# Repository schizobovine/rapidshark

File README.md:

# RapidShark
Nerf RapidStrike CS-18 mod using an Arduino and LiPo battery upgrade to rain
foamy annoyance upon one's enemies.

The name originally came from my initial idea to use a pair of NSR Shark 40krpm
motors, originally for 12V slot car racing. It quickly became a reference to
Randall Munroe's [XKCD comic about lowering one's standards for success as a
project wears on...]<https://xkcd.com/349/>

# Versions

This project has undergone a number of major and minor redesigns, and my
documentation isn't exactly the best, especially for earlier versions where I
assumed this would be a quick hack involving relatively little electronics
knowledge (oh, to be 3 years younger and less naive...).

* Mark I
*  Completed build
*  Used slightly larger motors: 24mm 12V 12850rpm [PAN14EE12AA1]<http://www.digikey.com/product-detail/en/PAN14EE12AA1/P14346-ND/2417070>
*  Covered cut-outs for above with some horribly done epoxy work
*  4S LiPo battery (14.8V nominal)
*  Flywheels ran directly off battery voltage
*  Rate of fire controlled via diodes (1N5209's?) in series
*  Segmented LED display only showed battery voltage.
*  Extremely noisy, had jamming issues especially at higher ROF
*  Very clumsy controls (giant knob on the side for ROF)
*  Overall, kinda crappy prototype

* Mark II
*  Never finished build
*  Originally going to be 2S LiPo based
*  Proved too noisy for reasonable use

* Mark III
*  Completed build
*  Same [PAN14EE12AA1]<http://www.digikey.com/product-detail/en/PAN14EE12AA1/P14346-ND/2417070> as in Mark I
*  Used heat gun to deform plastic to accomodate motors
*  4S LiPo battery (14.8V nominal)
*  Flywheels again directly off line voltage
*  Rate of fire controlled via stupidly big linear regulator (LM335, then LT1083)
*  Custom PCB from OSHPark for speed controller
*  Actually bothered to paint this one
*  Slightly better slide switch for ROF control
*  Added pushbutton laser "sight" because reasons
*  First attempt at ammo counter using SparkFun Pro Mini 5V to drive a 2 digit segmented display
*  Detected shots at first using IR LED & photodiode, but was too noisy so went to reed switch
*  Button panel for fiddling with/resetting counter
*  Counter was awesome but proved very unreliable in practice
*  Noticable voltage drop-out during flywheel spin-up

* Mark IV
*  Work in progess
*  Skipping paint job to make this one a "sleeper" model
*  Motors unselected but will be 130 Mabuchi form-factor to fit in existing case with little modification
*  Will feature two proper H-bridges, the [Pololu VNH5019 Motor Driver Carrier]<https://www.pololu.com/product/1451>
*  Since the H-bridges will be electronically controlled, switched to subminiature microswitches hooked up to uC (instead of giant 15A microswitches directly flipping current around)
*  [Adafruit Metro Mini]<https://www.adafruit.com/products/2590> as main controller
*  OLED display (either SparkFun Microview or Ye Olde Generic From Ebay)
*  IR interrupter for dart firing detection confirmation, in combination with mechanical position detection for the dart pusher.
*  Whole slew of small custom PCB's to aid in wiring

# License

* AVR C code (basically, everything under the firmware directory) is licensed under the GPLv2.0.
* Everything else is Creative Commons 4.0, Attribution-Share-Sharealike (CC-4.0-BY-SA)

# Acknowledgements

I would not be nearly as far along (or in the ICU from exploding batteries) if
not for the help and previous work & knowledge of
[torukmakto4]<http://torukmakto4.blogspot.co.uk/>; read some of the linked
posts below for a good breakdown of the basic fire control circuit in the
RapidStrike.

I also would like to thank the folks from Blastersmiths UK for their
information shared on [Diaries of a Nerf
Armorurer]<http://nerfarmourer.tumblr.com>, as it both provided inspiration,
guidance, and a lot of helpful pictures for this project.

# References

[The Dart Zone: Wiring and electrical practices]<http://torukmakto4.blogspot.co.uk/2013/04/tech-wiring-and-electrical-practices.html>
[The Dart Zone: Standard Rapidstrike, an Illustrated Guide]<http://torukmakto4.blogspot.co.uk/2013/10/standard-rapidstrike-illustrated-guide.html>
[The Dart Zone: Why compensating for resistance using additional voltage is bad design]<http://torukmakto4.blogspot.co.uk/2014/05/why-compensating-for-resistance-using.html>
[Diaries of a Nerf Armourer: 'Sharked' Rapidstrike CS-18 - Raja and Triakis]<http://nerfarmourer.tumblr.com/post/59029888581/sharked-rapidstrike-cs-18-raja-and-triakis>
[Diaries of a Nerf Armourer: NSR Shark 40 Necrospy]<http://nerfarmourer.tumblr.com/post/69776618533/nsr-shark-40-necrospy>
[Diaries of a Nerf Armourer: Rapidstrike Modification Guide]<http://nerfarmourer.tumblr.com/post/57957334515/rapidstrike-modification-guide-also-commissions>

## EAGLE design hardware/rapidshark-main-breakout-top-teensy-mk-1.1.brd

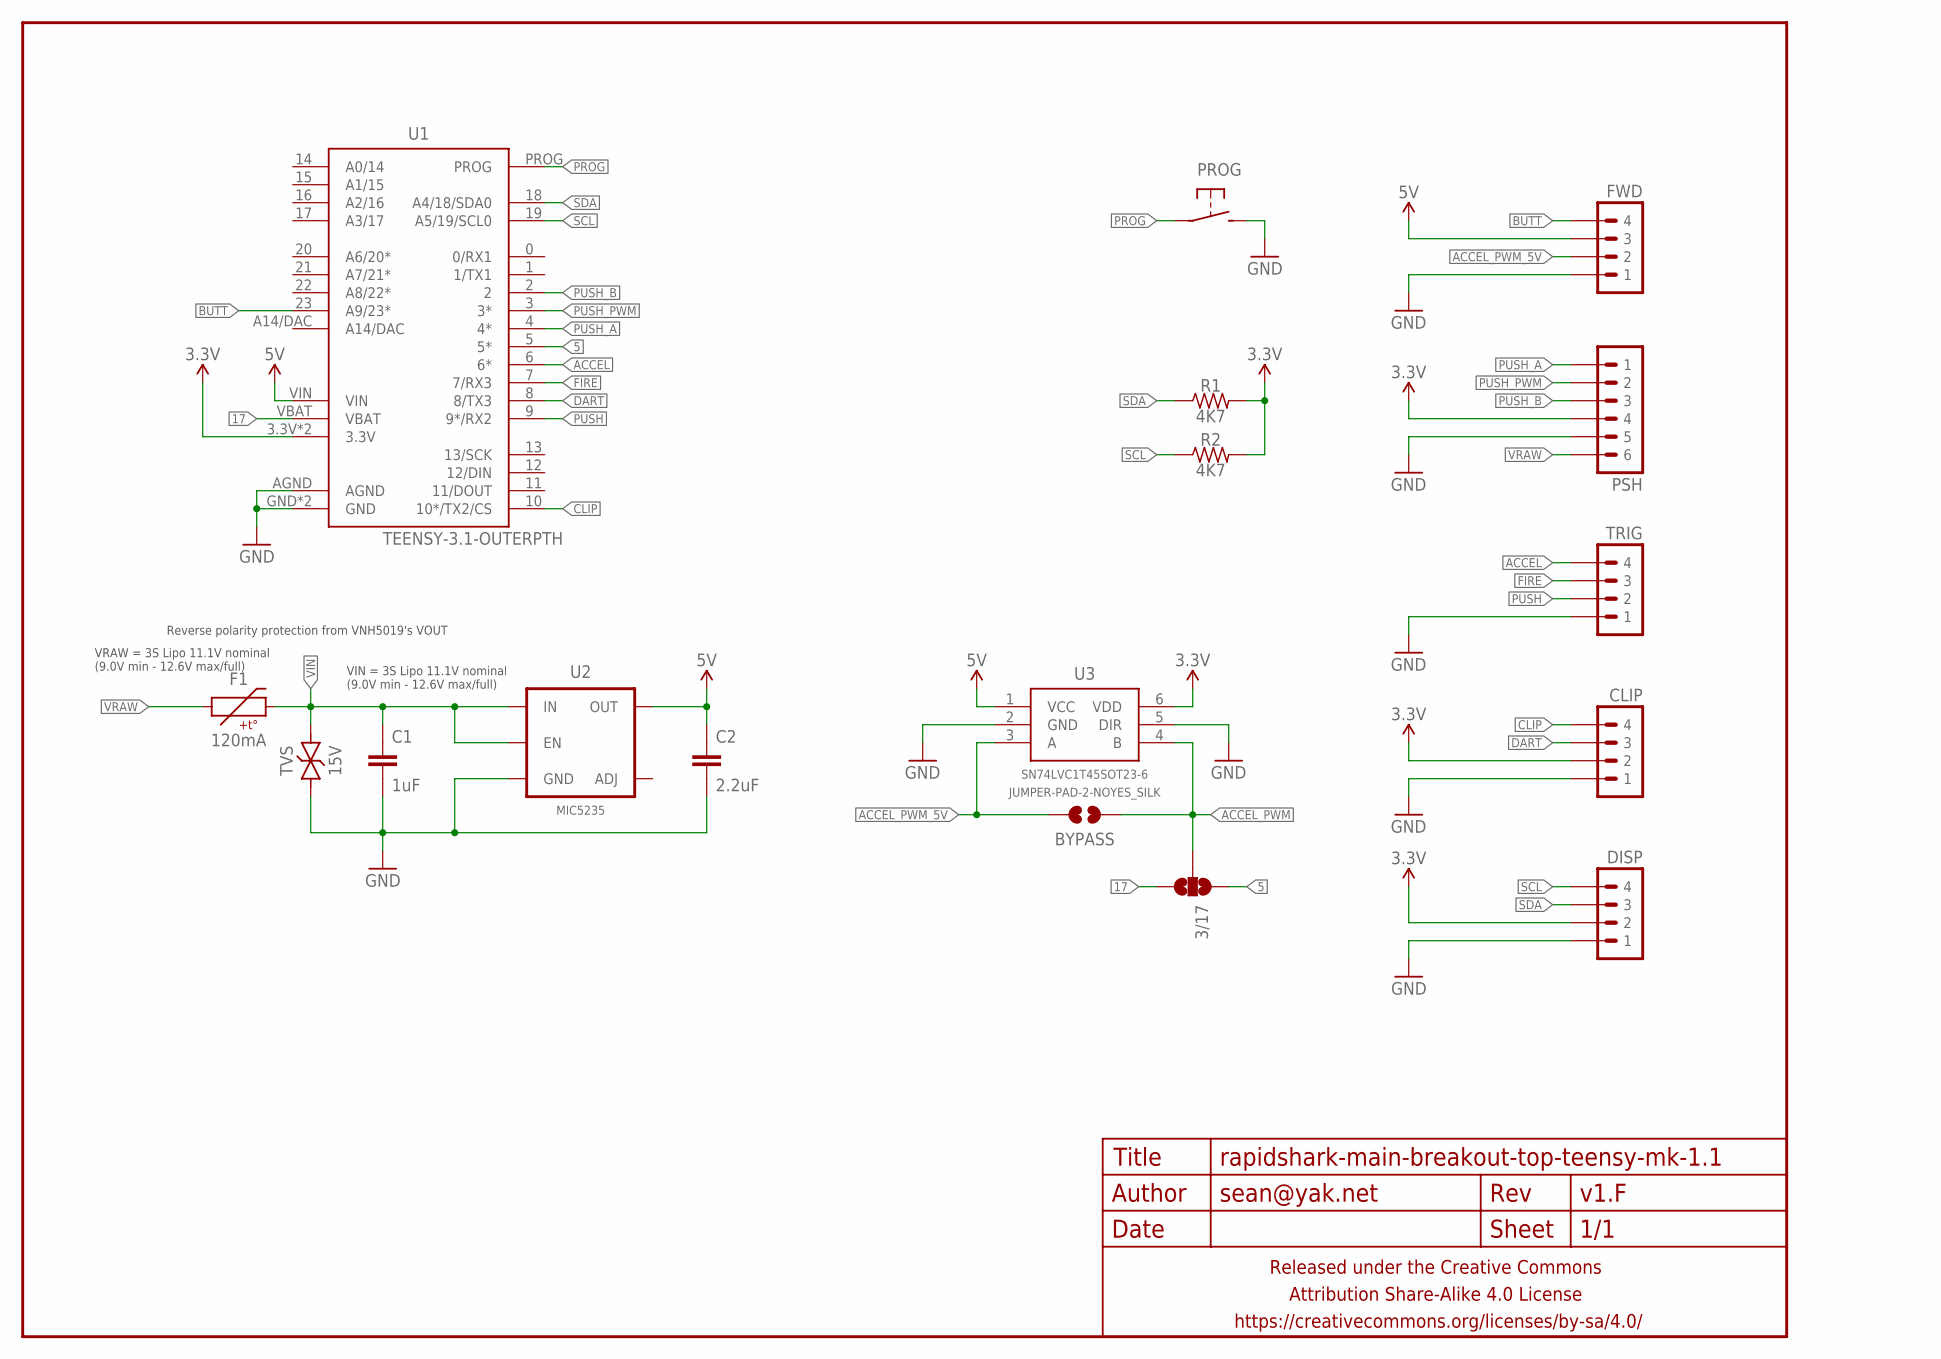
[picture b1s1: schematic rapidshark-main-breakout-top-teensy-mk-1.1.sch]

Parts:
3/17: JUMPER-PAD-3-NOSMALLER; PAD-JUMPER-3-NO_YES_SILK_FULL_BOX_SMALLER
BYPASS: JUMPER-PAD-2-NOYES_SILK; PAD-JUMPER-2-NO_YES_SILK
C1: 1uF; C0603-TIGHTER
C2: 2.2uF; C0603-TIGHTER
CLIP: M04JST-PTH-VERT; JST-4-PH-VERT-PTH
DISP: M04JST-PTH-VERT; JST-4-PH-VERT-PTH
F1: 120mA; PTC-1206
FRAME1: FRAME-LETTERNO_PACKAGE; DUMMY
FWD: M04JST-PTH-VERT; JST-4-PH-VERT-PTH
PROG: SPST-NO-TACTCK-PTS840-GK; TACTILE-SMD-CK-PTS840-GK
PSH: M06JST-PH-PTH-VERT; JST-6-PH-VERT-PTH
R1, R2: 4K7; R0603-TIGHTER
TRIG: M04JST-PTH-VERT; JST-4-PH-VERT-PTH
TVS: 15V; SMA-DIODE-TVS-BIDIR
U1: TEENSY-3.1-OUTERPTH; TEENSY-3.1_OUTERONLY
U2: MIC5235; SOT23-5
U3: SN74LVC1T45SOT23-6; SOT23-6

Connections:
3.3V: CLIP.2, DISP.2, PSH.4, R1.2, R2.2, U1.3.3V, U1.3V (3.3V), U3.6 (VDD)
5: 3/17.1, U1.5 (5*)
5V: C2.1, FWD.3, U1.VIN, U2.5 (OUT), U3.1 (VCC)
17: 3/17.3, U1.VBAT
ACCEL: TRIG.4, U1.6 (6*)
ACCEL_PWM: 3/17.2, BYPASS.1, U3.4 (B)
ACCEL_PWM_5V: BYPASS.2, FWD.2, U3.3 (A)
BUTT: FWD.4, U1.23 (A9/23*)
CLIP: CLIP.4, U1.10 (10*/TX2/CS)
DART: CLIP.3, U1.8 (8/TX3)
FIRE: TRIG.3, U1.7 (7/RX3)
GND: C1.2, C2.2, CLIP.1, DISP.1, FWD.1, PROG.3 (2), PROG.4 (2), PSH.5, TRIG.1, TVS.1, U1.AGND, U1.GND, U1.GND1 (GND), U2.2 (GND), U3.2 (GND), U3.5 (DIR)
PROG: PROG.1, PROG.2 (1), U1.PROG
PUSH: TRIG.2, U1.9 (9*/RX2)
PUSH_A: PSH.1, U1.4 (4*)
PUSH_B: PSH.3, U1.2
PUSH_PWM: PSH.2, U1.3 (3*)
SCL: DISP.4, R2.1, U1.19 (A5/19/SCL0)
SDA: DISP.3, R1.1, U1.18 (A4/18/SDA0)
VIN: C1.1, F1.2, TVS.2, U2.1 (IN), U2.3 (EN)
VRAW: F1.1, PSH.6

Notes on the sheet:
VIN = 3S Lipo 11.1V nominal (9.0V min - 12.6V max/full)
VRAW = 3S Lipo 11.1V nominal (9.0V min - 12.6V max/full)
Reverse polarity protection from VNH5019's VOUT

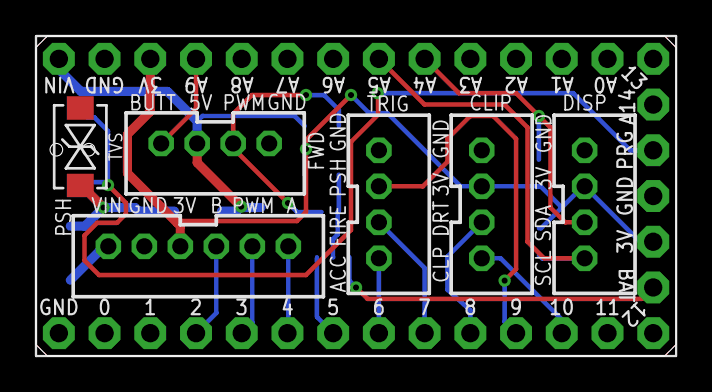
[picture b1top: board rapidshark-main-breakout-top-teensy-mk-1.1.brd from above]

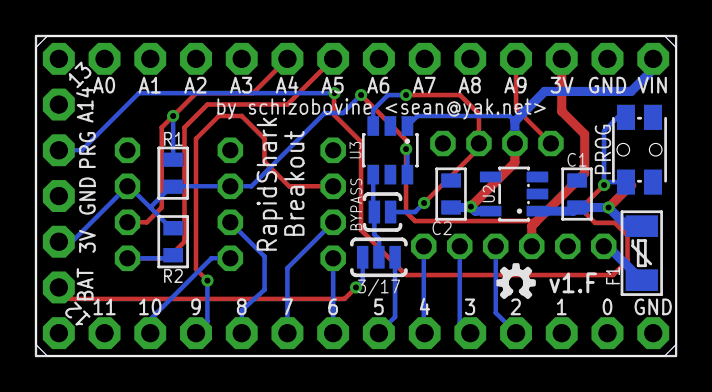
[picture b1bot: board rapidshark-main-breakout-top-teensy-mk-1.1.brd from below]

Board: 2 copper layers, 35.6 x 17.8 mm, 19 parts (12 on the bottom side), 21 nets.

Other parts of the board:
U$3: OSHWLOGO_TINY_SILKONLY

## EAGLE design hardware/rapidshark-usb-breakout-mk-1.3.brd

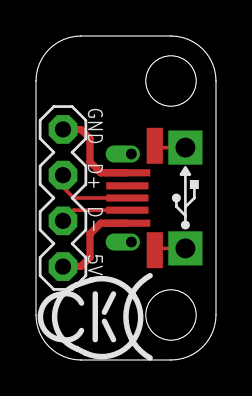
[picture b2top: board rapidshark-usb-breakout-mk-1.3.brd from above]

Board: 2 copper layers, 10.0 x 18.0 mm, 4 parts (1 on the bottom side), 4 nets.

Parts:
FRAME1: FRAME-LETTERNO_PACKAGE; DUMMY
JP1: M04PTH-CENTERED; 1X04-PTH-VERT-CENTER
U$1: COW_SMALL_NOTEXT
USB1: USB-AB-SHIELDFCI-10103594-USB-MICRO-B-EVENLESS; FCI-10103594-USB-MICRO-B-EVENLESS

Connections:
5V: JP1.4, USB1.1
DATA_M: JP1.3, USB1.2
DATA_P: JP1.2, USB1.3
GND: JP1.1, USB1.5, USB1.SHIELD@1, USB1.SHIELD@2, USB1.SHIELD@3, USB1.SHIELD@4, USB1.SHIELD@5, USB1.SHIELD@6

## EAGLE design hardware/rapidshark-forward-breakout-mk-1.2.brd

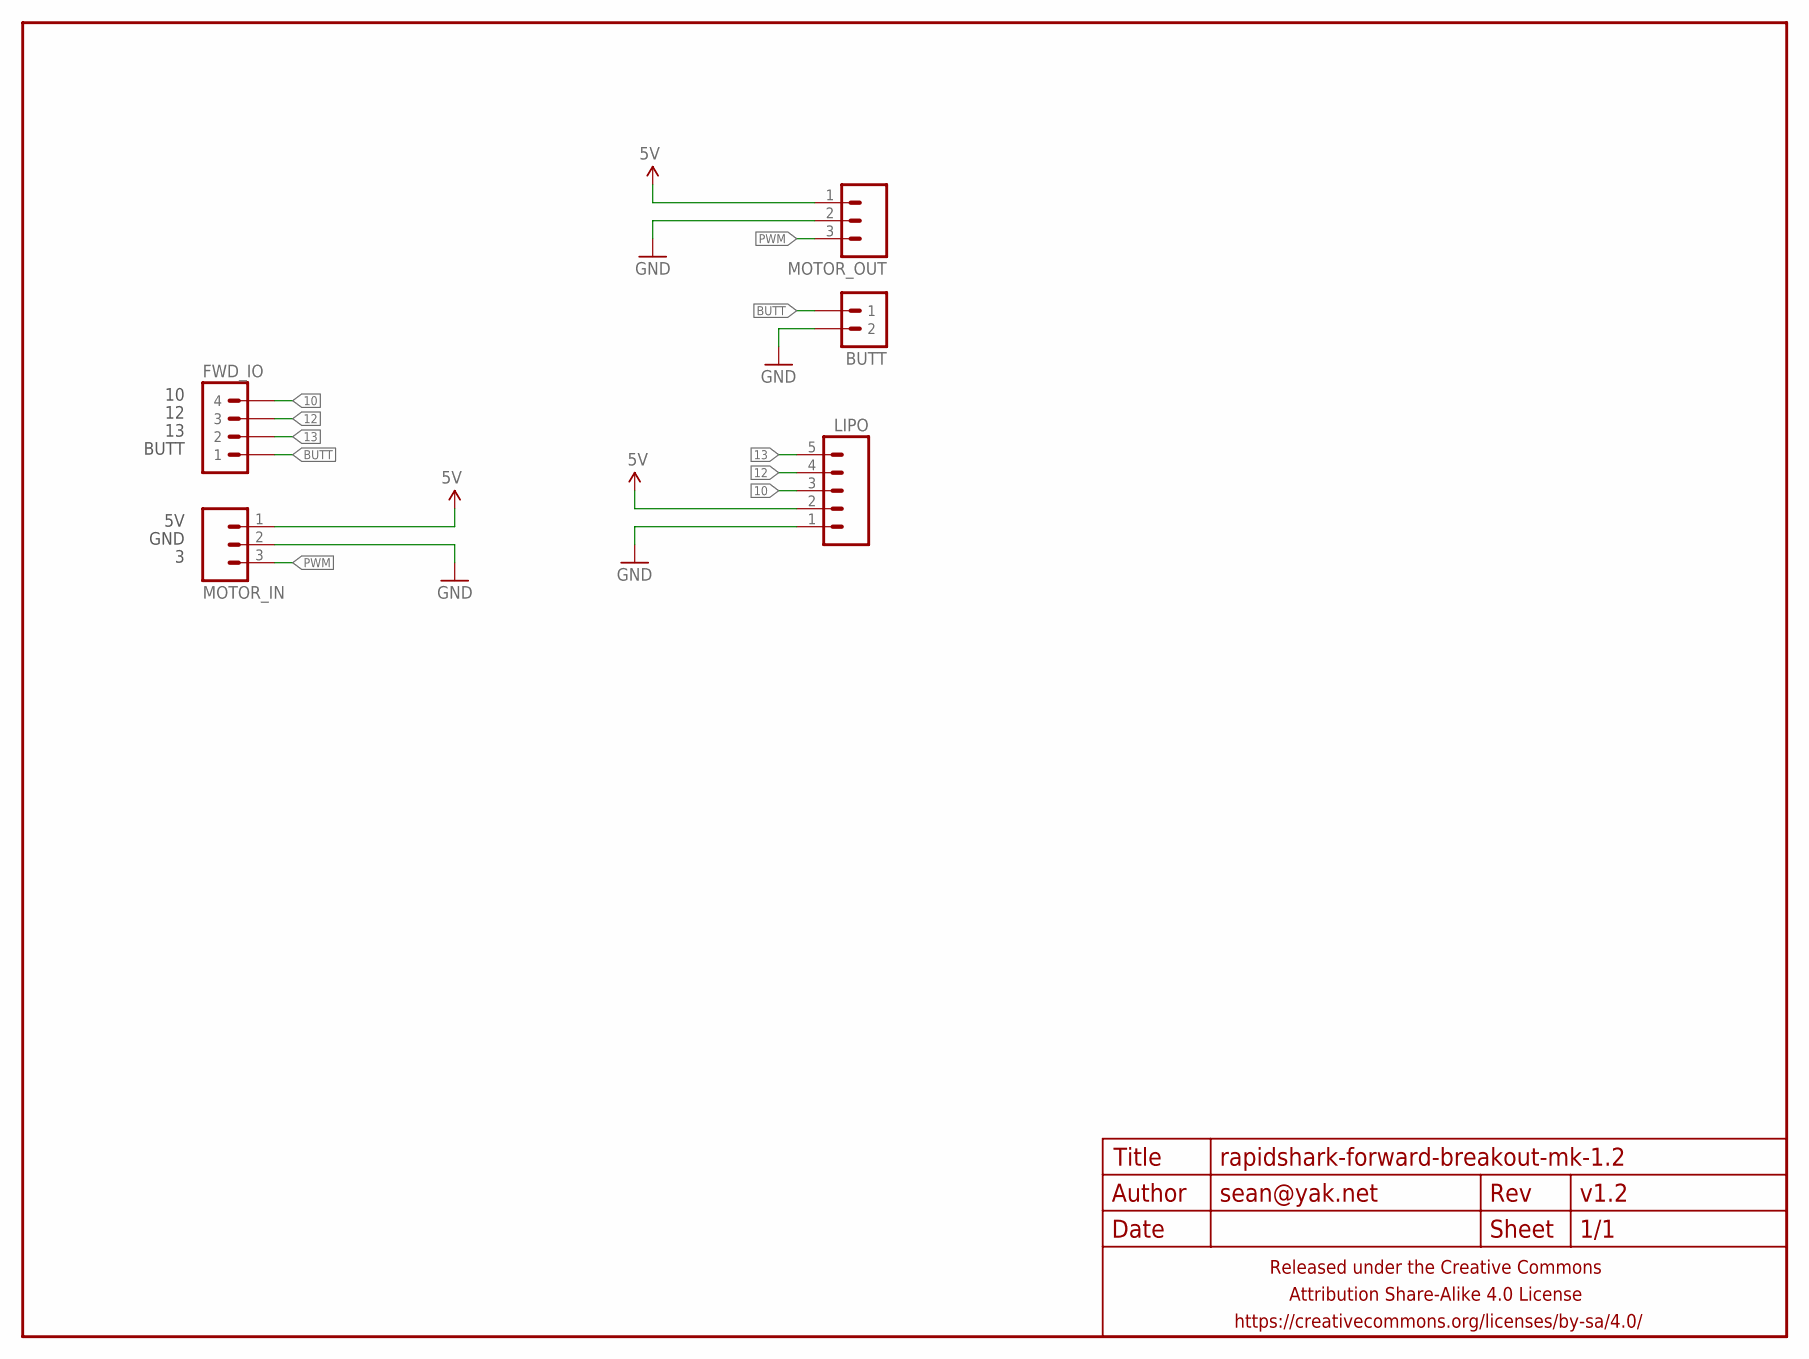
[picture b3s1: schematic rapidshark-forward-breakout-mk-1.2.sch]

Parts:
BUTT: M02JST-PTH-VERT; JST-2-PH-VERT-PTH
FRAME1: FRAME-LETTERNO_PACKAGE; DUMMY
FWD_IO: M04JST-PTH-VERT; JST-4-PH-VERT-PTH
LIPO: M05JST-PH-VERT-PTH; JST-5-PH-VERT-PTH
MOTOR_IN: M03JST-PTH-VERT; JST-3-PH-VERT-PTH
MOTOR_OUT: M03JST-PTH-VERT; JST-3-PH-VERT-PTH

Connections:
5V: LIPO.2, MOTOR_IN.1, MOTOR_OUT.1
10: FWD_IO.4, LIPO.3
12: FWD_IO.3, LIPO.4
13: FWD_IO.2, LIPO.5
BUTT: BUTT.1, FWD_IO.1
GND: BUTT.2, LIPO.1, MOTOR_IN.2, MOTOR_OUT.2
PWM: MOTOR_IN.3, MOTOR_OUT.3

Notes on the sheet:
GND
BUTT

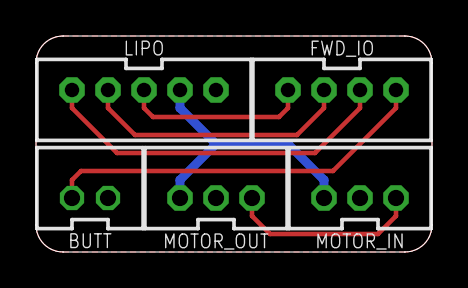
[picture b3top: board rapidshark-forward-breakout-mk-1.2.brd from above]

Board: 2 copper layers, 22.0 x 12.0 mm, 6 parts (1 on the bottom side), 7 nets.

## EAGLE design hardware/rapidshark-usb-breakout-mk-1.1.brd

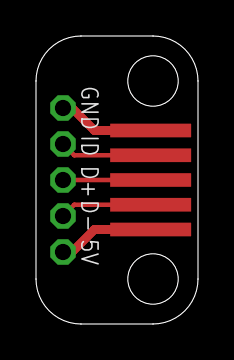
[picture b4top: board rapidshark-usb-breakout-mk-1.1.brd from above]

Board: 2 copper layers, 9.0 x 16.0 mm, 3 parts (1 on the bottom side), 5 nets.

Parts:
FRAME1: FRAME-LETTERNO_PACKAGE; DUMMY
JP1: M052MMPTH; 1X05-0.9X2MM-PTH
U1: ADAFRUIT_USB_PANEL_MOUNT

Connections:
5V: JP1.5, U1.5
DATA_M: JP1.4, U1.4
DATA_P: JP1.3, U1.3
GND: JP1.1, U1.1
ID: JP1.2, U1.2

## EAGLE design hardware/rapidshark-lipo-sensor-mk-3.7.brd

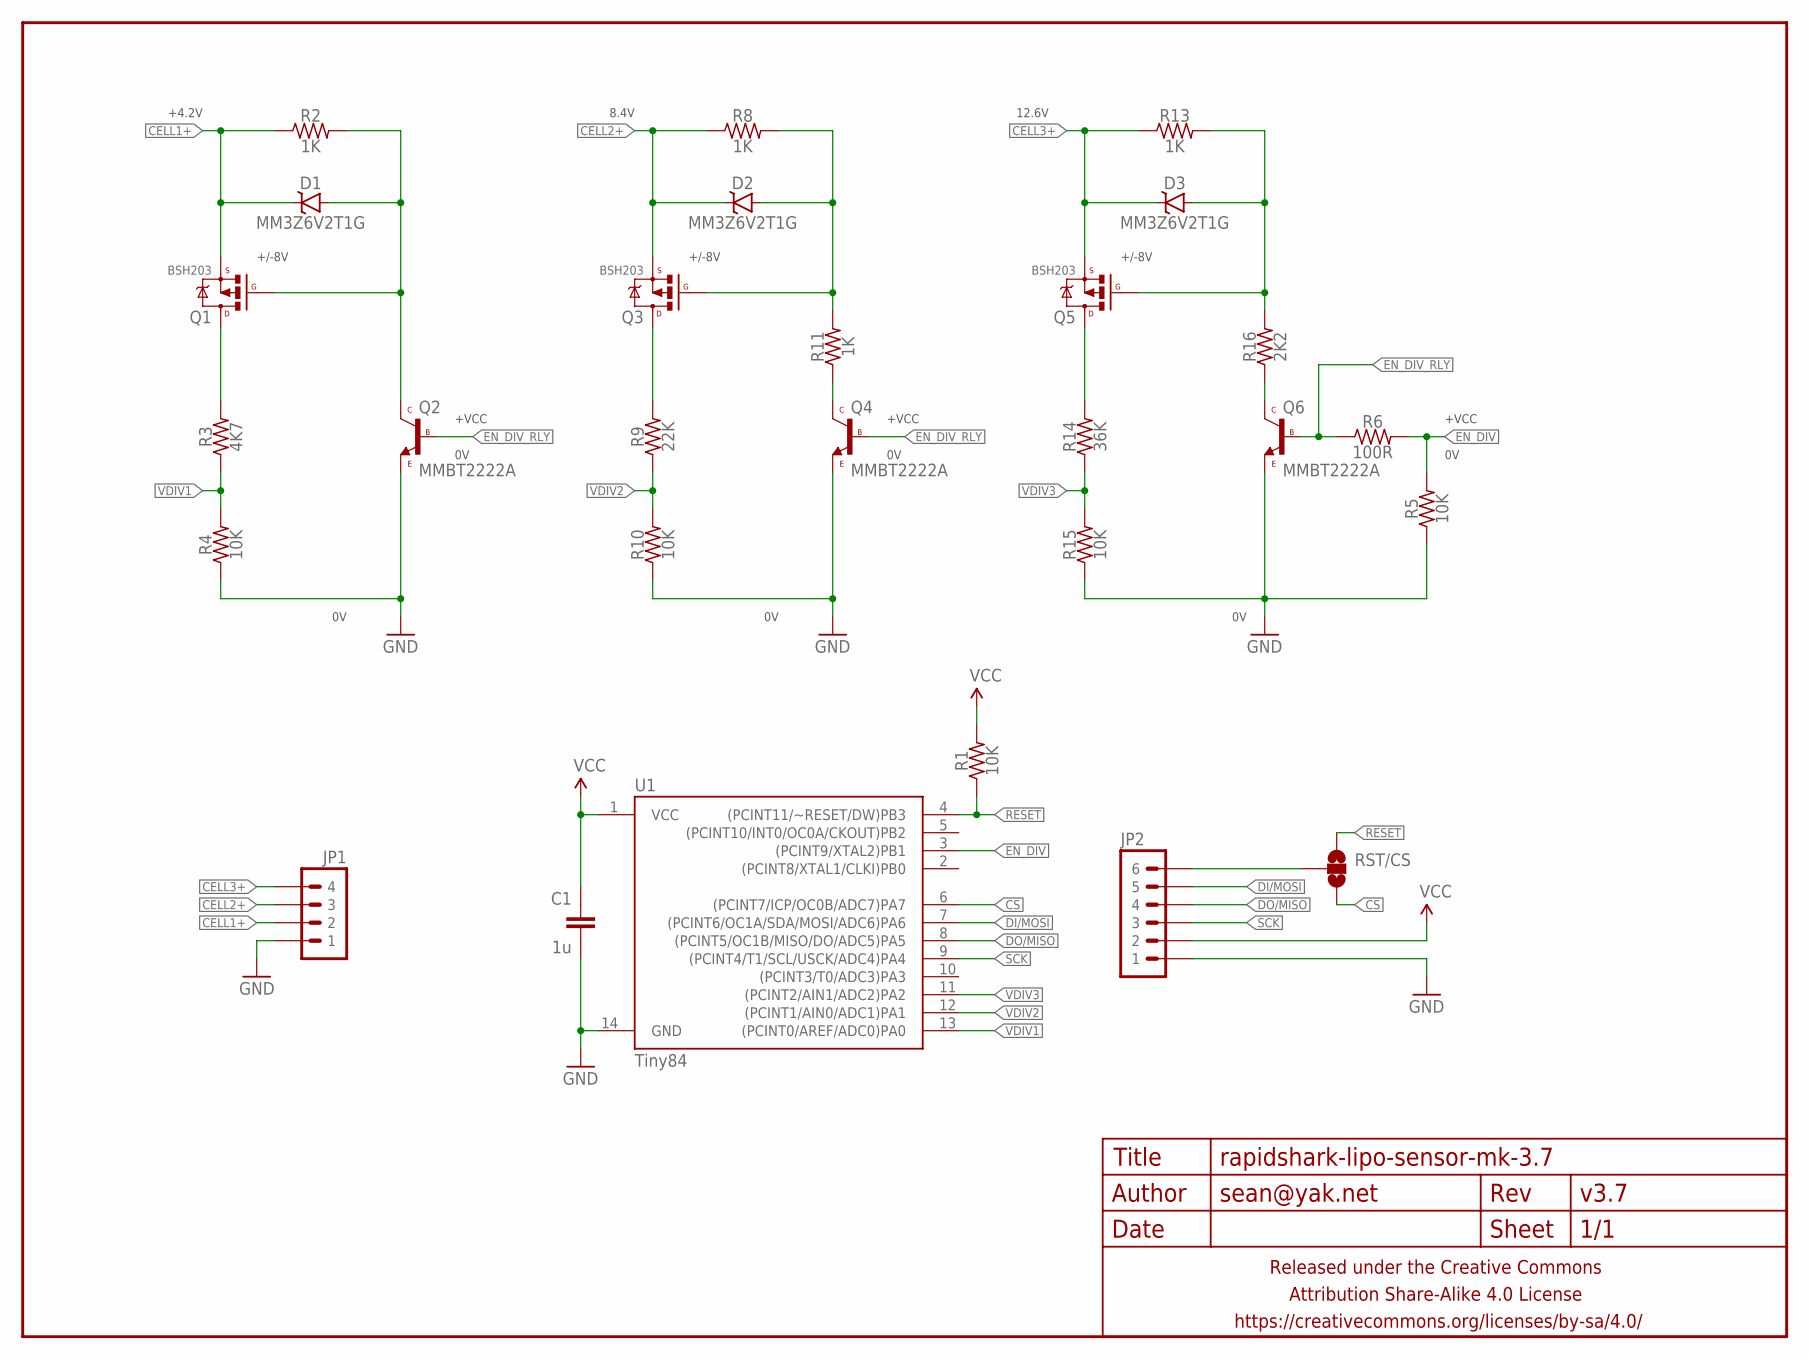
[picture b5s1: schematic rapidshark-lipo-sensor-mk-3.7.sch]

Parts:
C1: 1u; C0603-TIGHTER
D1, D2, D3: MM3Z6V2T1G; SOD323-ZENNER
FRAME1: FRAME-LETTERNO_PACKAGE; DUMMY
JP1: M04JST_XH_RA; JST-4-XH-RA-PTH
JP2: M06PTH_CENTERED; 1X06_CENTERED
Q1, Q3, Q5: BSH203; SOT23
Q2, Q4, Q6: MMBT2222A; SOT23
R1, R4, R5, R10, R15: 10K; R0603-TIGHTER
R2, R8, R11, R13: 1K; R0603-TIGHTER
R3: 4K7; R0603-TIGHTER
R6: 100R; R0603-TIGHTER
R9: 22K; R0603-TIGHTER
R14: 36K; R0603-TIGHTER
R16: 2K2; R0603-TIGHTER
RST/CS: JUMPER-PAD-3-NOFULL_BOX_SILK; PAD-JUMPER-3-NO_YES_SILK_FULL_BOX
U1: Tiny84; SO14

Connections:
CELL1+: D1.C, JP1.2, Q1.2 (S), R2.1
CELL2+: D2.C, JP1.3, Q3.2 (S), R8.1
CELL3+: D3.C, JP1.4, Q5.2 (S), R13.1
CS: RST/CS.3, U1.6 ((PCINT7/ICP/OC0B/ADC7)PA7)
DI/MOSI: JP2.5, U1.7 ((PCINT6/OC1A/SDA/MOSI/ADC6)PA6)
DO/MISO: JP2.4, U1.8 ((PCINT5/OC1B/MISO/DO/ADC5)PA5)
EN_DIV: R5.2, R6.2, U1.3 ((PCINT9/XTAL2)PB1)
EN_DIV_RLY: Q2.1 (B), Q4.1 (B), Q6.1 (B), R6.1
GND: C1.2, JP1.1, JP2.1, Q2.2 (E), Q4.2 (E), Q6.2 (E), R4.1, R5.1, R10.1, R15.1, U1.14 (GND)
unnamed: Q4.3 (C), R11.1
unnamed: Q3.3 (D), R9.2
unnamed: Q5.3 (D), R14.2
unnamed: D2.A, Q3.1 (G), R8.2, R11.2
unnamed: Q1.3 (D), R3.2
unnamed: D3.A, Q5.1 (G), R13.2, R16.2
unnamed: Q6.3 (C), R16.1
unnamed: D1.A, Q1.1 (G), Q2.3 (C), R2.2
RESET: R1.1, RST/CS.1, U1.4 ((PCINT11/~RESET/DW)PB3)
RST/CS: JP2.6, RST/CS.2
SCK: JP2.3, U1.9 ((PCINT4/T1/SCL/USCK/ADC4)PA4)
VCC: C1.1, JP2.2, R1.2, U1.1 (VCC)
VDIV1: R3.1, R4.2, U1.13 ((PCINT0/AREF/ADC0)PA0)
VDIV2: R9.1, R10.2, U1.12 ((PCINT1/AIN0/ADC1)PA1)
VDIV3: R14.1, R15.2, U1.11 ((PCINT2/AIN1/ADC2)PA2)

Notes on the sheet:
+4.2V
8.4V
12.6V
+VCC
+/-8V

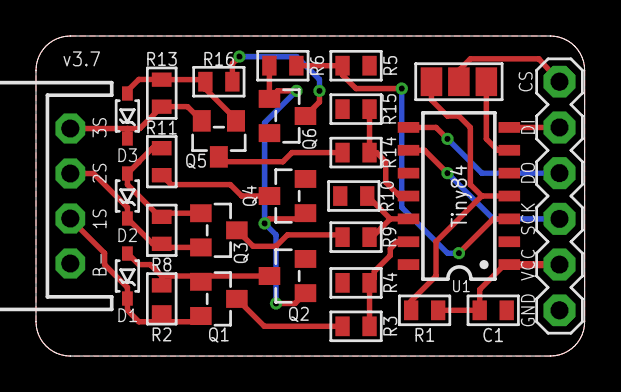
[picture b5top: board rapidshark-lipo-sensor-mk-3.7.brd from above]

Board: 2 copper layers, 30.5 x 17.8 mm, 29 parts (0 on the bottom side), 24 nets.

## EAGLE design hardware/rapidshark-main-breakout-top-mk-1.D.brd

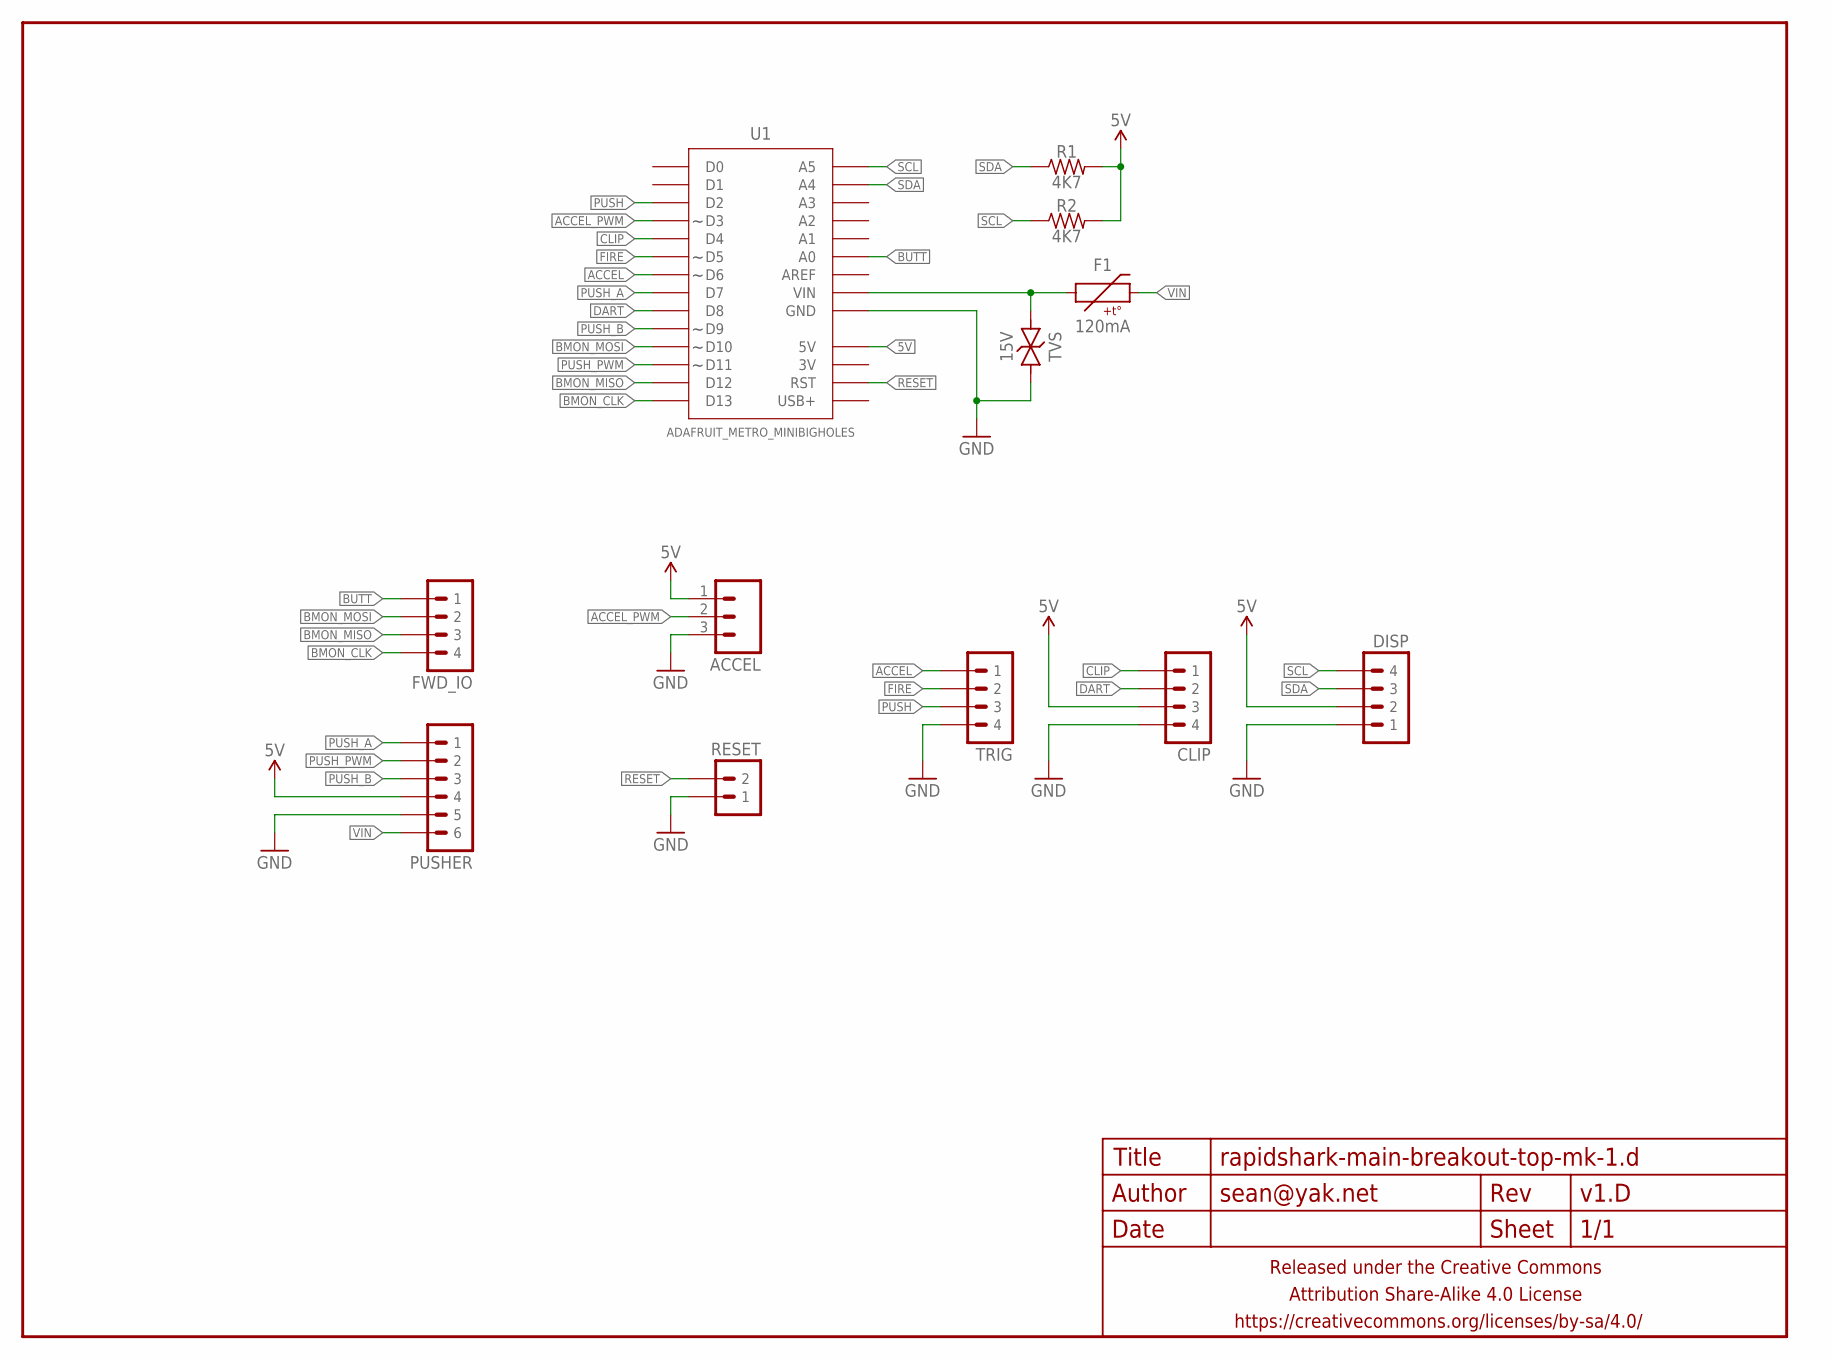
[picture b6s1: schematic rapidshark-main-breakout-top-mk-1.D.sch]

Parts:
ACCEL: M03JST-PTH-VERT-CENTERED; JST-3-PH-VERT-PTH-CENTERED
CLIP: M04JST-PTH-VERT; JST-4-PH-VERT-PTH
DISP: M04JST-PTH-VERT; JST-4-PH-VERT-PTH
F1: 120mA; PTC-1206
FRAME1: FRAME-LETTERNO_PACKAGE; DUMMY
FWD_IO: M04JST-PTH-VERT; JST-4-PH-VERT-PTH
PUSHER: M06JST-PH-PTH-VERT; JST-6-PH-VERT-PTH
R1, R2: 4K7; R0603-TIGHTER
RESET: M02JST-PTH-VERT; JST-2-PH-VERT-PTH
TRIG: M04JST-PTH-VERT; JST-4-PH-VERT-PTH
TVS: 15V; SMA-DIODE-TVS-BIDIR
U1: ADAFRUIT_METRO_MINIBIGHOLES; ADAFRUIT_METRO_MINI_BIGHOLES

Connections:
5V: ACCEL.1, CLIP.3, DISP.2, PUSHER.4, R1.2, R2.2, U1.18 (5V)
ACCEL: TRIG.1, U1.7 (D6)
ACCEL_PWM: ACCEL.2, U1.4 (D3)
BMON_CLK: FWD_IO.4, U1.14 (D13)
BMON_MISO: FWD_IO.3, U1.13 (D12)
BMON_MOSI: FWD_IO.2, U1.11 (D10)
BUTT: FWD_IO.1, U1.23 (A0)
CLIP: CLIP.1, U1.5 (D4)
DART: CLIP.2, U1.9 (D8)
FIRE: TRIG.2, U1.6 (D5)
GND: ACCEL.3, CLIP.4, DISP.1, PUSHER.5, RESET.1, TRIG.4, TVS.1, U1.19 (GND), U1.20 (GND)
unnamed: F1.1, TVS.2, U1.21 (VIN)
PUSH: TRIG.3, U1.3 (D2)
PUSH_A: PUSHER.1, U1.8 (D7)
PUSH_B: PUSHER.3, U1.10 (D9)
PUSH_PWM: PUSHER.2, U1.12 (D11)
RESET: RESET.2, U1.16 (RST)
SCL: DISP.4, R2.1, U1.28 (A5)
SDA: DISP.3, R1.1, U1.27 (A4)
VIN: F1.2, PUSHER.6

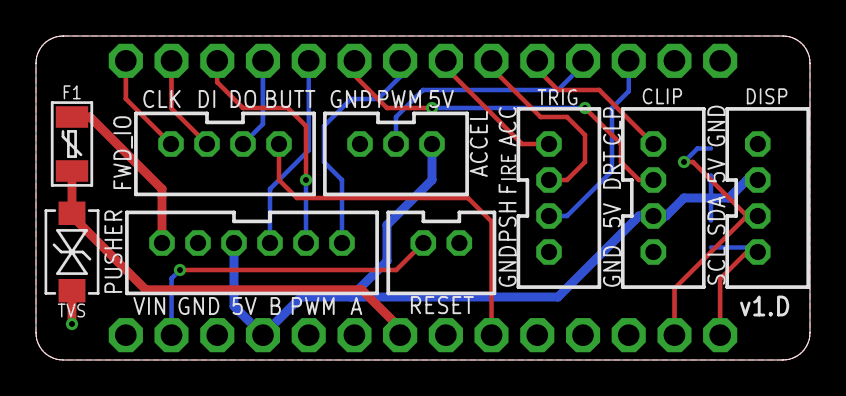
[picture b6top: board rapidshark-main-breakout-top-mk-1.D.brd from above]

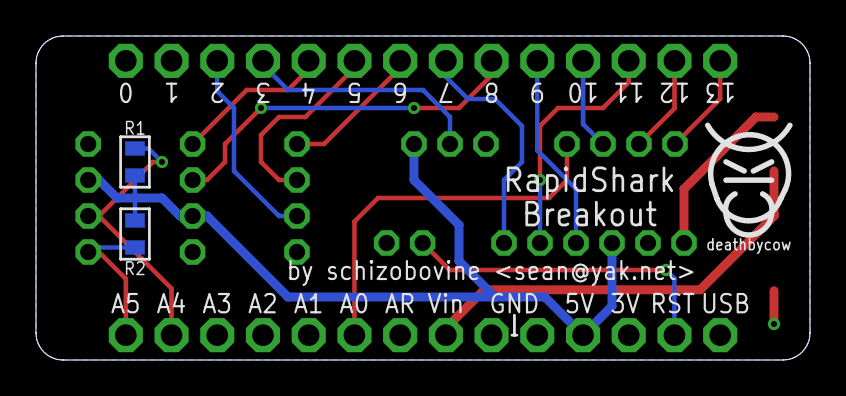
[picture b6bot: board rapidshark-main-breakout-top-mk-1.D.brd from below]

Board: 2 copper layers, 43.0 x 18.0 mm, 14 parts (4 on the bottom side), 20 nets.

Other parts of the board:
U$2: COW_SMALL

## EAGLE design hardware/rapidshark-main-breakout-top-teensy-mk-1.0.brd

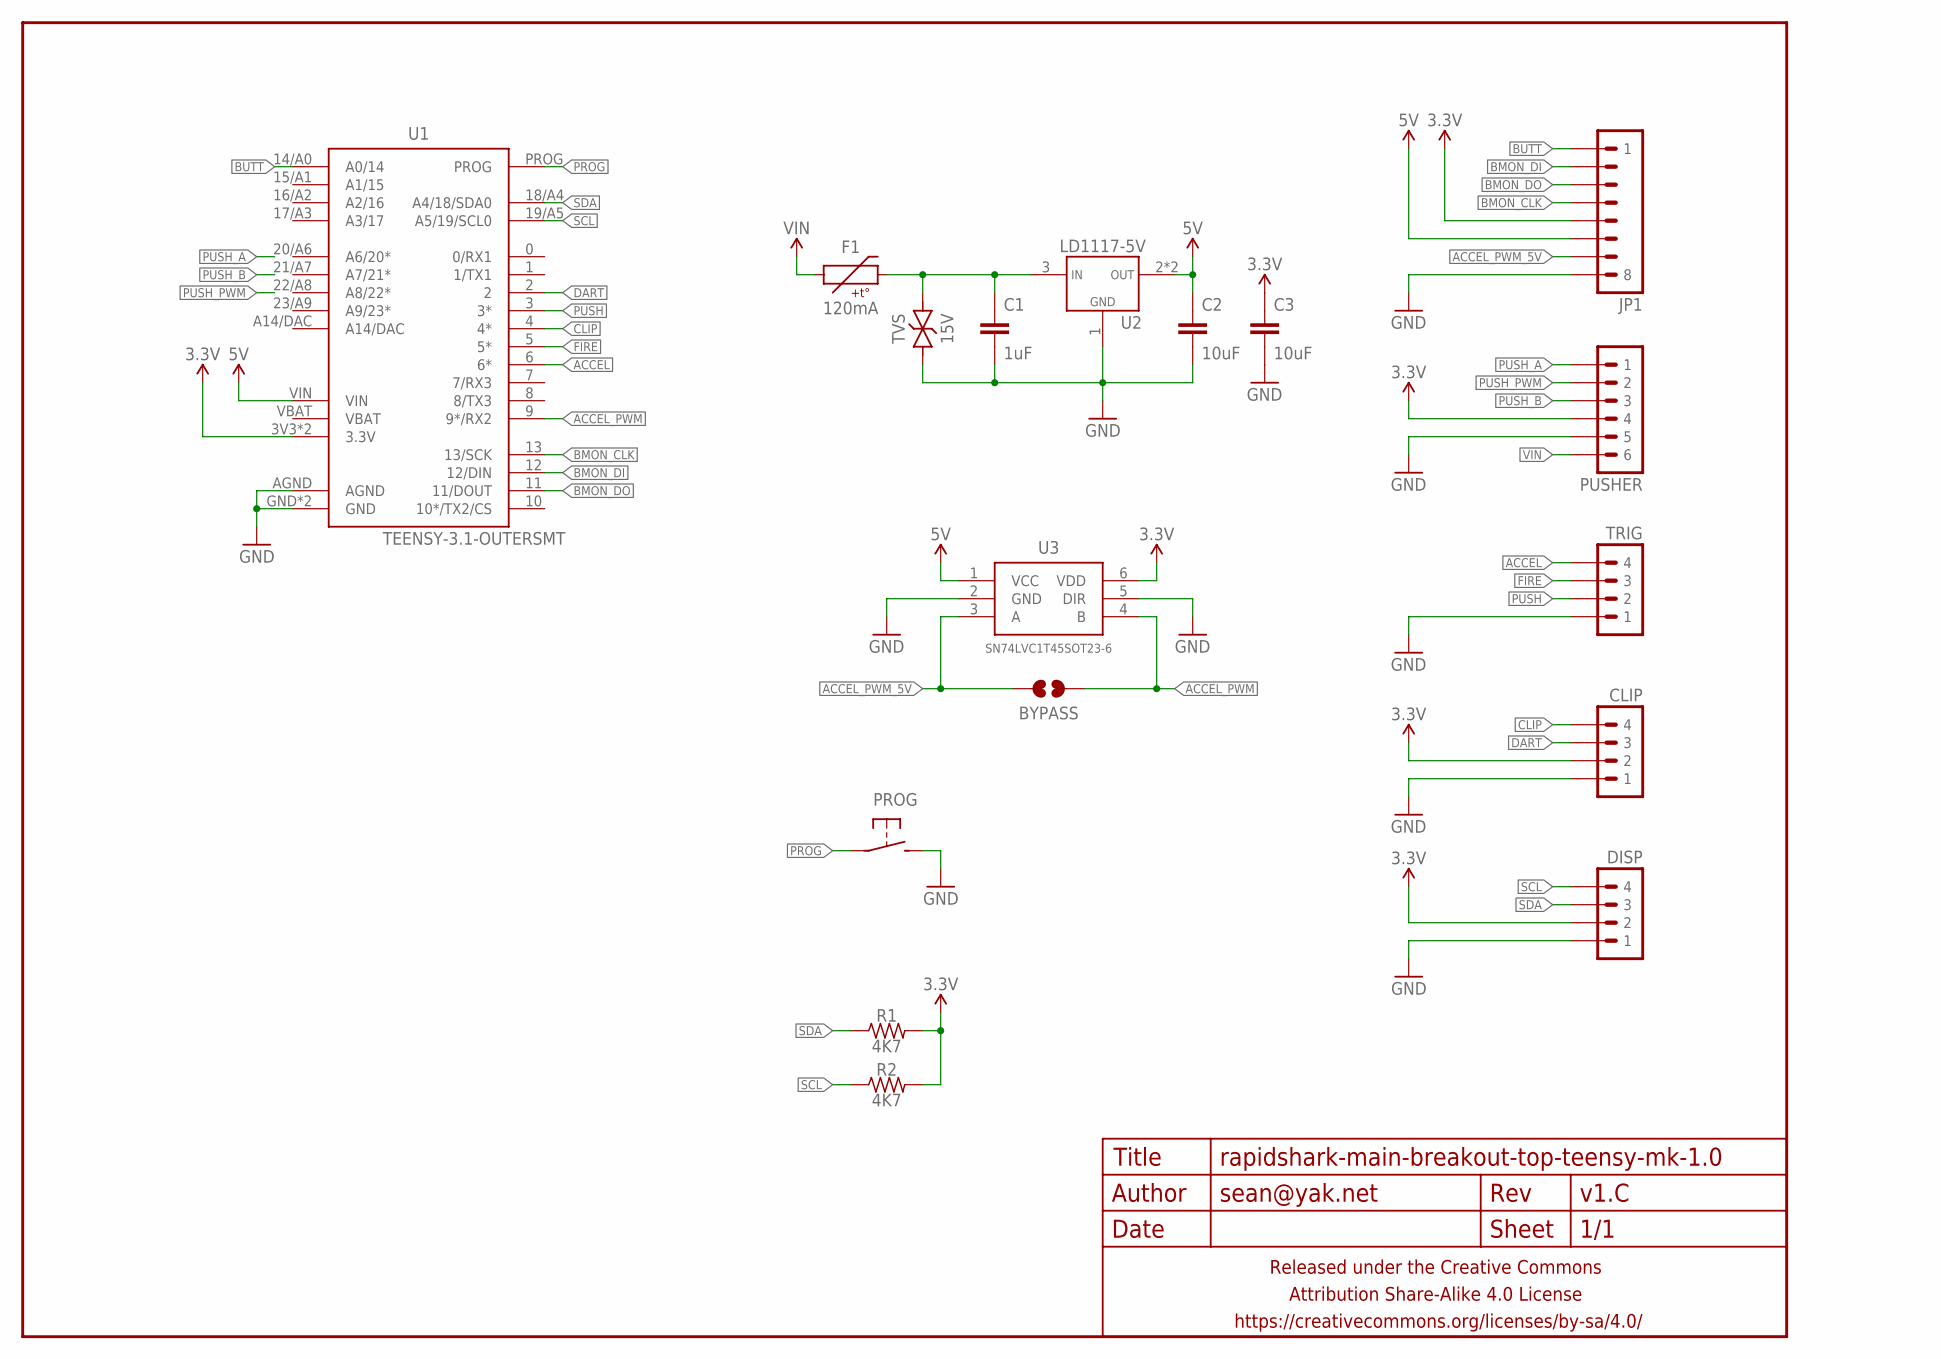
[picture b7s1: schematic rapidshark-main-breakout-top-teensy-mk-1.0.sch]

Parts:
BYPASS: JUMPER-PAD-2-NOYES_SILK; PAD-JUMPER-2-NO_YES_SILK
C1: 1uF; C0603
C2, C3: 10uF; C0805
CLIP: M04JST-PTH-VERT; JST-4-PH-VERT-PTH
DISP: M04JST-PTH-VERT; JST-4-PH-VERT-PTH
F1: 120mA; PTC-1206
FRAME1: FRAME-LETTERNO_PACKAGE; DUMMY
JP1: M08SMD-RA-MALE-2MM; 1X08_SMD_RA_MALE_2MM
PROG: SPST-NO-TACTCK-PTS840-GK; TACTILE-SMD-CK-PTS840-GK
PUSHER: M06JST-PH-PTH-VERT; JST-6-PH-VERT-PTH
R1, R2: 4K7; R0603-TIGHTER
TRIG: M04JST-PTH-VERT; JST-4-PH-VERT-PTH
TVS: 15V; SMA-DIODE-TVS-BIDIR
U1: TEENSY-3.1-OUTERSMT; TEENSY-3.1_SMT_BOTTOM_OUTERONLY
U2: LD1117-5V; SOT223
U3: SN74LVC1T45SOT23-6; SOT23-6

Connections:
3.3V: C3.1, CLIP.2, DISP.2, JP1.5, PUSHER.4, R1.2, R2.2, U1.3V3 (3.3V), U1.3V3@1 (3.3V), U3.6 (VDD)
5V: C2.1, JP1.6, U1.VIN, U2.2 (VOUT), U2.4 (VOUT), U3.1 (VCC)
ACCEL: TRIG.4, U1.6 (6*)
ACCEL_PWM: BYPASS.1, U1.9 (9*/RX2), U3.4 (B)
ACCEL_PWM_5V: BYPASS.2, JP1.7, U3.3 (A)
BMON_CLK: JP1.4, U1.13 (13/SCK)
BMON_DI: JP1.2, U1.12 (12/DIN)
BMON_DO: JP1.3, U1.11 (11/DOUT)
BUTT: JP1.1, U1.14/A0 (A0/14)
CLIP: CLIP.4, U1.4 (4*)
DART: CLIP.3, U1.2
FIRE: TRIG.3, U1.5 (5*)
GND: C1.2, C2.2, C3.2, CLIP.1, DISP.1, JP1.8, PROG.3 (2), PROG.4 (2), PUSHER.5, TRIG.1, TVS.1, U1.AGND, U1.GND, U1.GND@1 (GND), U2.1 (GND), U3.2 (GND), U3.5 (DIR)
unnamed: C1.1, F1.2, TVS.2, U2.3 (VIN)
PROG: PROG.1, PROG.2 (1), U1.PROG
PUSH: TRIG.2, U1.3 (3*)
PUSH_A: PUSHER.1
PUSH_B: PUSHER.3
PUSH_PWM: PUSHER.2
SCL: DISP.4, R2.1, U1.19/A5 (A5/19/SCL0)
SDA: DISP.3, R1.1, U1.18/A4 (A4/18/SDA0)
VIN: F1.1, PUSHER.6

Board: 2 copper layers, 20 parts (5 on the bottom side), 19 nets, no tracks yet.

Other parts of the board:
U$2: COW_SMALL
U$3: OSHWLOGO_TINY_SILKONLY

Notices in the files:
hardware/rapidshark-lipo-sensor-mk-3.7.brd:
CC-BY-SA-4.0
parts and their libraries:
A_butts: Released under the Creative Commons Attribution Share-Alike 4.0 License
A_butts: https://creativecommons.org/licenses/by-sa/4.0
A_butts: Released under the Creative Commons
